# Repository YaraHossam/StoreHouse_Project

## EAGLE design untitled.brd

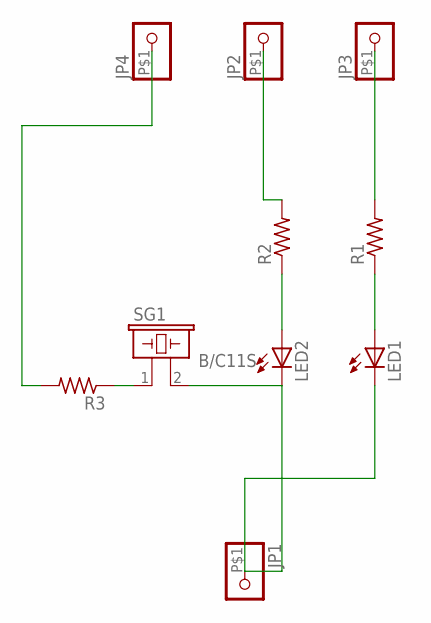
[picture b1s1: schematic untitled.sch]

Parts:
JP1, JP2, JP3, JP4: PINHD-1X1-BIGPOGO; 1X1-BIGPOGO
LED1, LED2: LEDB152; Q62902-B152
R1, R2, R3: FLIPFLOP-RES; 0805-THM
SG1: B/C11S

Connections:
unnamed: JP1.P$1, LED1.K (C), LED2.K (C), SG1.2
unnamed: JP3.P$1, R1.2
unnamed: LED1.A, R1.1
unnamed: LED2.A, R2.1
unnamed: JP2.P$1, R2.2
unnamed: R3.1, SG1.1
unnamed: JP4.P$1, R3.2

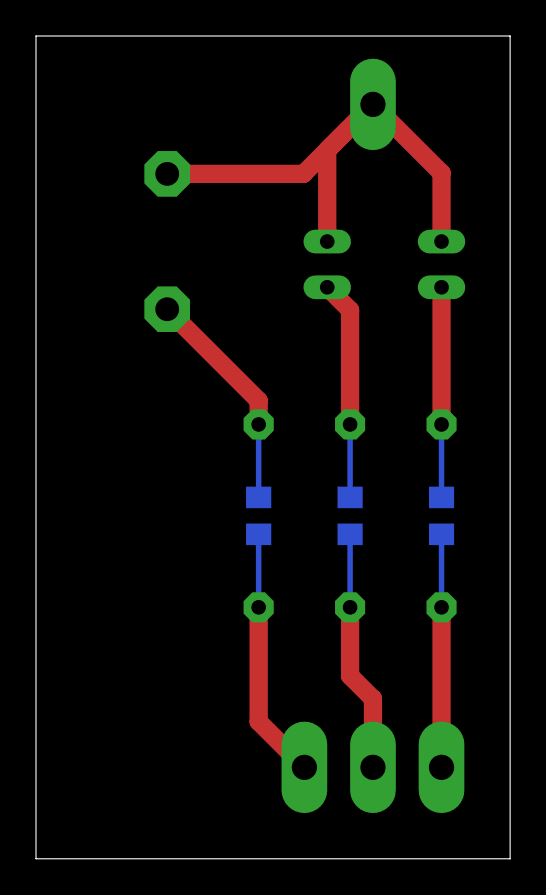
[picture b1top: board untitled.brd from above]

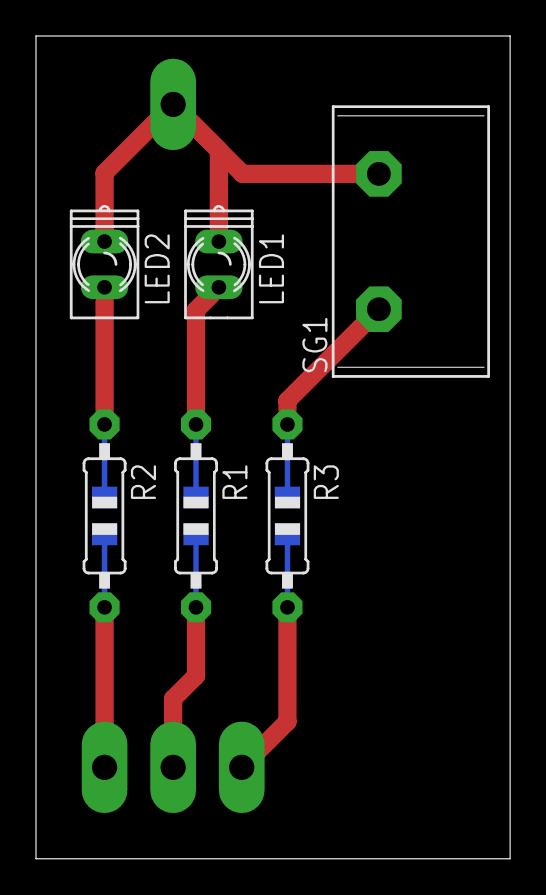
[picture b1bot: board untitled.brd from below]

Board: 2 copper layers, 26.3 x 45.7 mm, 10 parts (10 on the bottom side), 7 nets.

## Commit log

2020-11-08 Assembly Project
